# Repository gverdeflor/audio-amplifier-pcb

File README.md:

# audio-amplifier-pcb
A PCB design for a class D audio amplifier. Designed in EAGLE by Garth Verdeflor & Sergio Bobadilla.

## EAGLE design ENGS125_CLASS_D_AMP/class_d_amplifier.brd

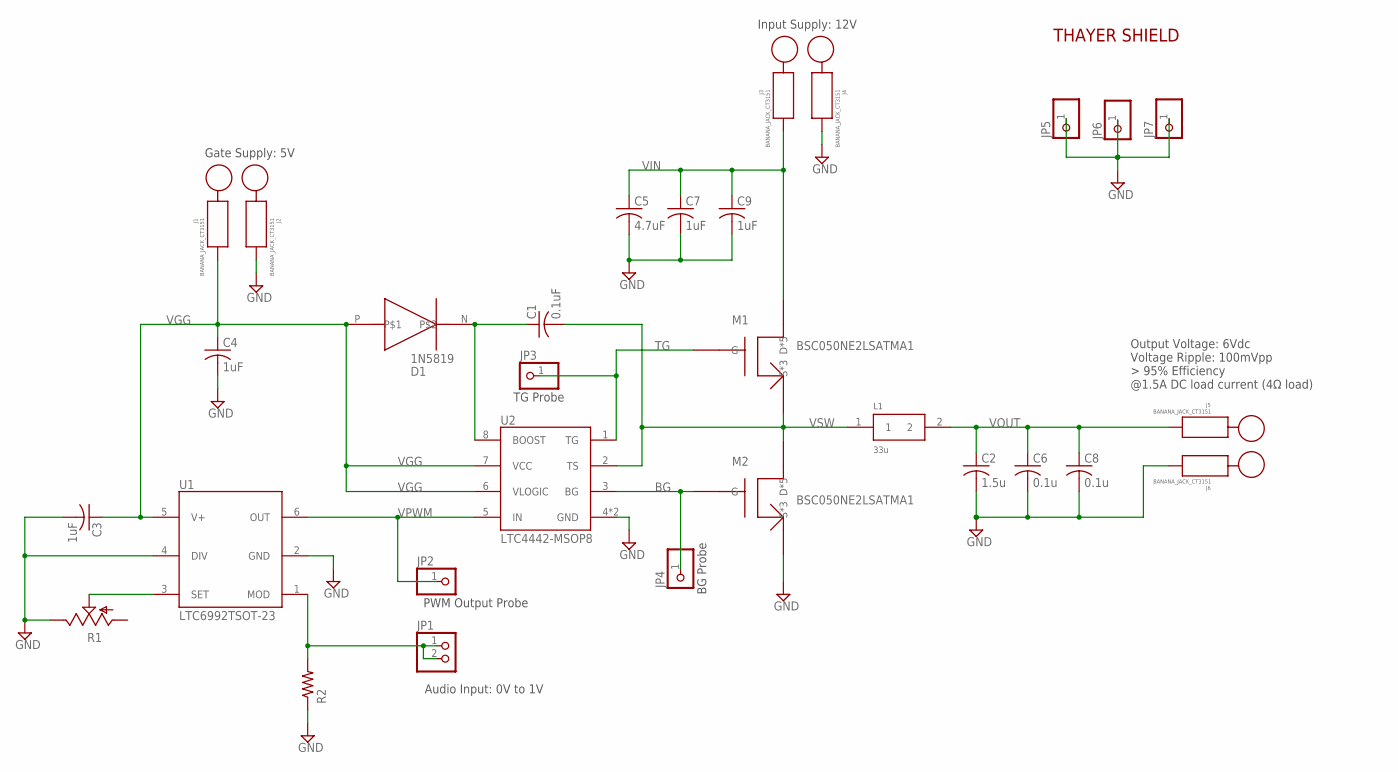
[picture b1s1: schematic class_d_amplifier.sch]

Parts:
C1: 0.1uF; C0805
C2: 1.5u; C1206
C3, C4, C7, C9: 1uF; C0805
C5: 4.7uF; C1206
C6, C8: 0.1u; C0805
D1: 1N5819; SOD123
J1, J2, J3, J4, J5, J6: BANANA_JACK_CT3151; CT3151SP2_PCB_MOUNT
JP1: PINHD-1X2; 1X02
JP2, JP3, JP4, JP5, JP6, JP7: PINHD-1X1; 1X01
L1: 33u; SER2900
M1, M2: BSC050NE2LSATMA1; PD-TDSON-8
R1: TRIM_US-CT6; CT6
R2: R-US; R0805
U1: LTC6992TSOT-23; TSOT23-6
U2: LTC4442-MSOP8; LTC4442
U$1: THAYER

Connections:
BG: JP4.1, M2.4 (G), U2.3 (BG)
BOOST: C1.1, D1.N, U2.8 (BOOST)
GND: C2.2, C3.2, C4.2, C5.2, C6.2, C7.2, C8.2, C9.2, J2.P$1, J2.P$2, J2.P$3, J2.P$4, J4.P$1, J4.P$2, J4.P$3, J4.P$4, J6.P$1, J6.P$2, J6.P$3, J6.P$4, JP5.1, JP6.1, JP7.1, M2.1 (S*3), M2.2 (S*3), M2.3 (S*3), R1.E, R2.1, U1.2 (GND), U1.4 (DIV), U2.4 (GND), U2.9 (GND)
unnamed: R1.S, U1.3 (SET)
unnamed: JP1.1, JP1.2, R2.2, U1.1 (MOD)
TG: JP3.1, M1.4 (G), U2.1 (TG)
VGG: C3.1, C4.1, D1.P, J1.P$1, J1.P$2, J1.P$3, J1.P$4, U1.5 (V+), U2.6 (VLOGIC), U2.7 (VCC)
VIN: C5.1, C7.1, C9.1, J3.P$1, J3.P$2, J3.P$3, J3.P$4, M1.5 (D*5), M1.6 (D*5), M1.7 (D*5), M1.8 (D*5), M1.9 (D*5)
VOUT: C2.1, C6.1, C8.1, J5.P$1, J5.P$2, J5.P$3, J5.P$4, L1.2
VPWM: JP2.1, U1.6 (OUT), U2.5 (IN)
VSW: C1.2, L1.1, M1.1 (S*3), M1.2 (S*3), M1.3 (S*3), M2.5 (D*5), M2.6 (D*5), M2.7 (D*5), M2.8 (D*5), M2.9 (D*5), U2.2 (TS)

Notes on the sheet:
Input Supply: 12V
Gate Supply: 5V
Audio Input: 0V to 1V
PWM Output Probe
Output Voltage: 6Vdc Voltage Ripple: 100mVpp > 95% Efficiency @1.5A DC load current (4Ω load)
TG Probe
BG Probe

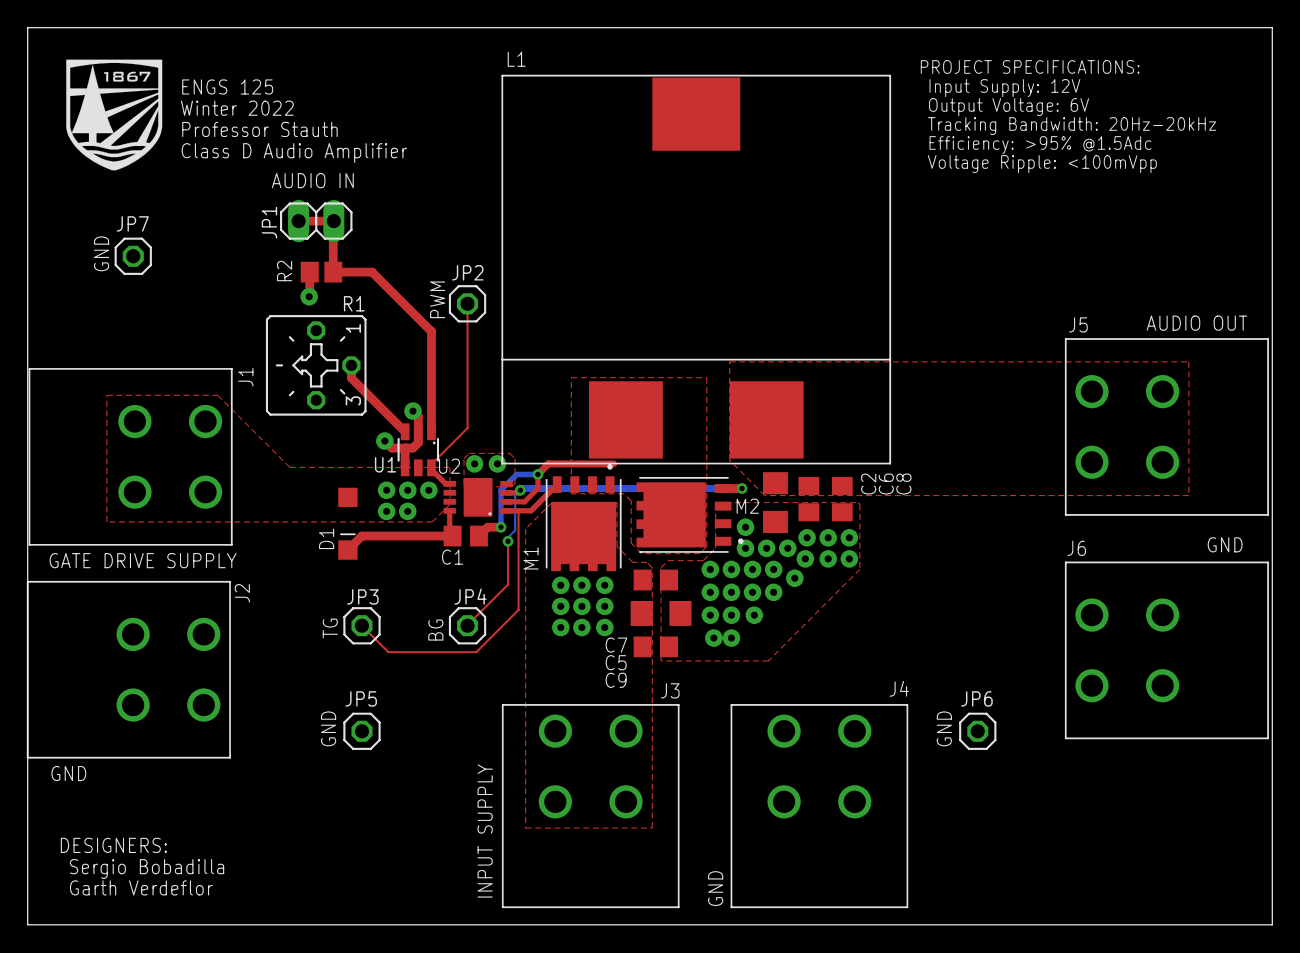
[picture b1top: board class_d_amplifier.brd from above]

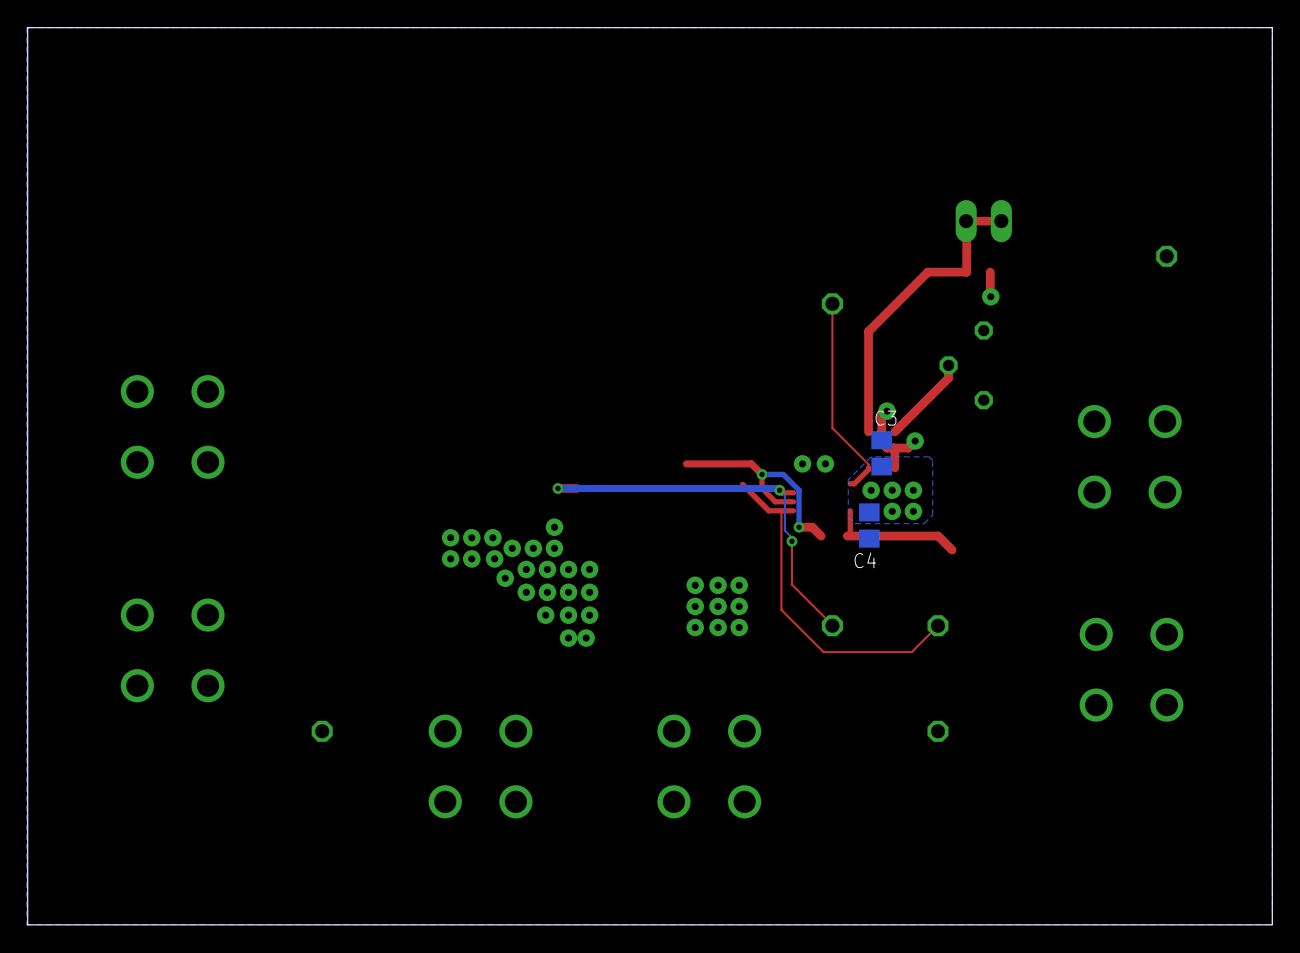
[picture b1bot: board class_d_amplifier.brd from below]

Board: 2 copper layers, 89.8 x 64.8 mm, 31 parts (2 on the bottom side), 11 nets.

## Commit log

2022-02-14 Set up and initialized project files
2022-02-15 Confirming access to repo.
2022-02-15 Added local class library to project
2022-02-15 Started schematic capture from lab carryover
2022-02-15 Generated board and set DRC rules
2022-02-18 Added updated class library with additional footprints
2022-02-18 Added banana jacks and edited schematic.
2022-02-18 Added switch optimization spreadsheet
2022-02-18 Updated package for LTC6992 (PWM modulator)
2022-02-18 Replaced Rset with trim potentiometer
2022-02-18 Added pin header for PWM output probe
2022-02-18 Added Project spice file and Powertrain Tracking png.
2022-02-18 Added footprint for switch. Added switch to schematic.
2022-02-19 Reorganized simulation and calculation files
2022-02-19 Added switches to optimization calculation sheet
2022-02-19 Initial placement of switching node components
2022-02-19 Generatedtop layer power polygons and placed vias
2022-02-19 Removed component values from silkscreen
2022-02-19 Initial placement of banana jack connectors
2022-02-19 Generated bottom layer GND plane
2022-02-19 Condensed board shape after replacement of connectors
2022-02-19 Routed power polygons to connectors
2022-02-19 Refined placement of gate driver and PWM modulator ICs
2022-02-19 Routed top layer signals
2022-02-19 Began bottom layer routing for IC bypass caps
2022-02-20 Added silkscreen project information
2022-02-20 Added silkscreen labels for banana jack connectors
2022-02-20 Added silkscreen labels for pin headers
2022-02-20 Finished routing bypass caps on bottom layer
2022-02-20 Resolved DRC errors from minor unrouted nets
2022-02-21 Edited VGG polygon and IC bypass cap posititons.
2022-02-21 Fixed top layer polygon corners
2022-02-21 Added updated library with Thayer silkscreen logo
2022-02-21 Added Thayer shield to silkscreen on layout
2022-02-21 Reformatted silkscreen info with logo
2022-02-21 Implemented edits from discussion with Stauth: GND pins, Gate pins, and extra input cap.
2022-02-22 Replaced gate driver IC with LTC4442
2022-02-22 Added converter specs to silkscreen
2022-02-22 Rerouted gate driver IC for different component footprint
2022-02-22 Reorganized gate drive layout to minimize signal length and GND plane cutouts.
2022-02-22 Added in NEW library with updated LTC4442 footprint.
2022-02-22 Reorganized gate driver layout to account for fixed pin connections.
2022-02-22 Updated MOSFET symbol to use single pins for multiple pads.
2022-02-22 Minor routing and silkscreen fixes
2022-02-22 Fixed polygon corners and reference designators
2022-02-23 Included powertrain simulationresults
2022-03-09 Added efficiency and frequency sweep calculations
2022-03-09 Resolved frequency sweep magnitude plot
2022-03-09 Updated efficiency calculations
2022-03-09 Added revised excel project file
2022-03-10 Minor revisions to passive components calculation
